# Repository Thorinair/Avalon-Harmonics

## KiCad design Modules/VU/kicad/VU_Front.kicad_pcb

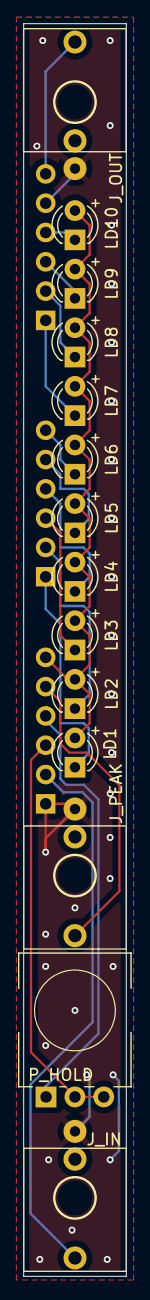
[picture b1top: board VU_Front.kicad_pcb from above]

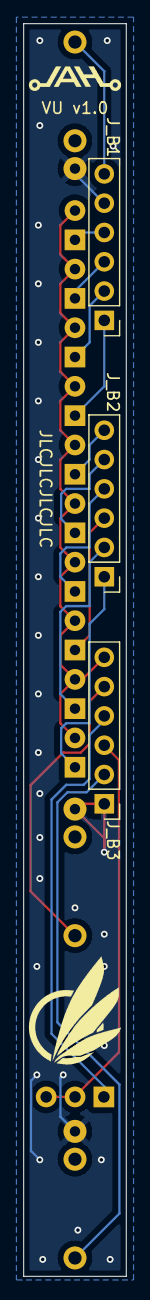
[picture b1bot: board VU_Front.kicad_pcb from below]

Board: 2 copper layers, 8.9 x 108.6 mm, 17 parts (3 on the bottom side), 17 nets.

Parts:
J_B1, J_B2, J_B3: Conn_01x06_Female; PinHeader_1x06_P2.54mm_Vertical
J_IN: PJ301M-12
J_OUT: PJ301M-12
J_PEAK: PJ301M-12
LD1, LD2, LD3, LD4, LD5: LED (YELLOW); LED_D3.0mm_FlatTop
LD6, LD7, LD8: LED (ORANGE); LED_D3.0mm_FlatTop
LD9, LD10: LED (RED); LED_D3.0mm_FlatTop
P_HOLD: A1M; Potentiometer Alpha RD901F-40-00D NoSides

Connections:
+5V: J_B3.6, LD1.2 (A), LD2.2 (A), LD3.2 (A), LD4.2 (A), LD5.2 (A), LD6.2 (A), LD7.2 (A), LD8.2 (A), LD9.2 (A), LD10.2 (A)
GND: J_B1.5, J_B3.1, J_IN.GND, J_OUT.GND, J_PEAK.GND
unnamed: J_B1.1, LD7.1 (K)
unnamed: J_B1.2, LD8.1 (K)
unnamed: J_B1.3, LD9.1 (K)
unnamed: J_B1.4, LD10.1 (K)
unnamed: J_B1.6, J_OUT.SIG
unnamed: J_B2.1, LD1.1 (K)
unnamed: J_B2.2, LD2.1 (K)
unnamed: J_B2.3, LD3.1 (K)
unnamed: J_B2.4, LD4.1 (K)
unnamed: J_B2.5, LD5.1 (K)
unnamed: J_B2.6, LD6.1 (K)
unnamed: J_B3.2, J_IN.SIG
unnamed: J_B3.3, P_HOLD.2, P_HOLD.3
unnamed: J_B3.4, P_HOLD.1
unnamed: J_B3.5, J_PEAK.SIG

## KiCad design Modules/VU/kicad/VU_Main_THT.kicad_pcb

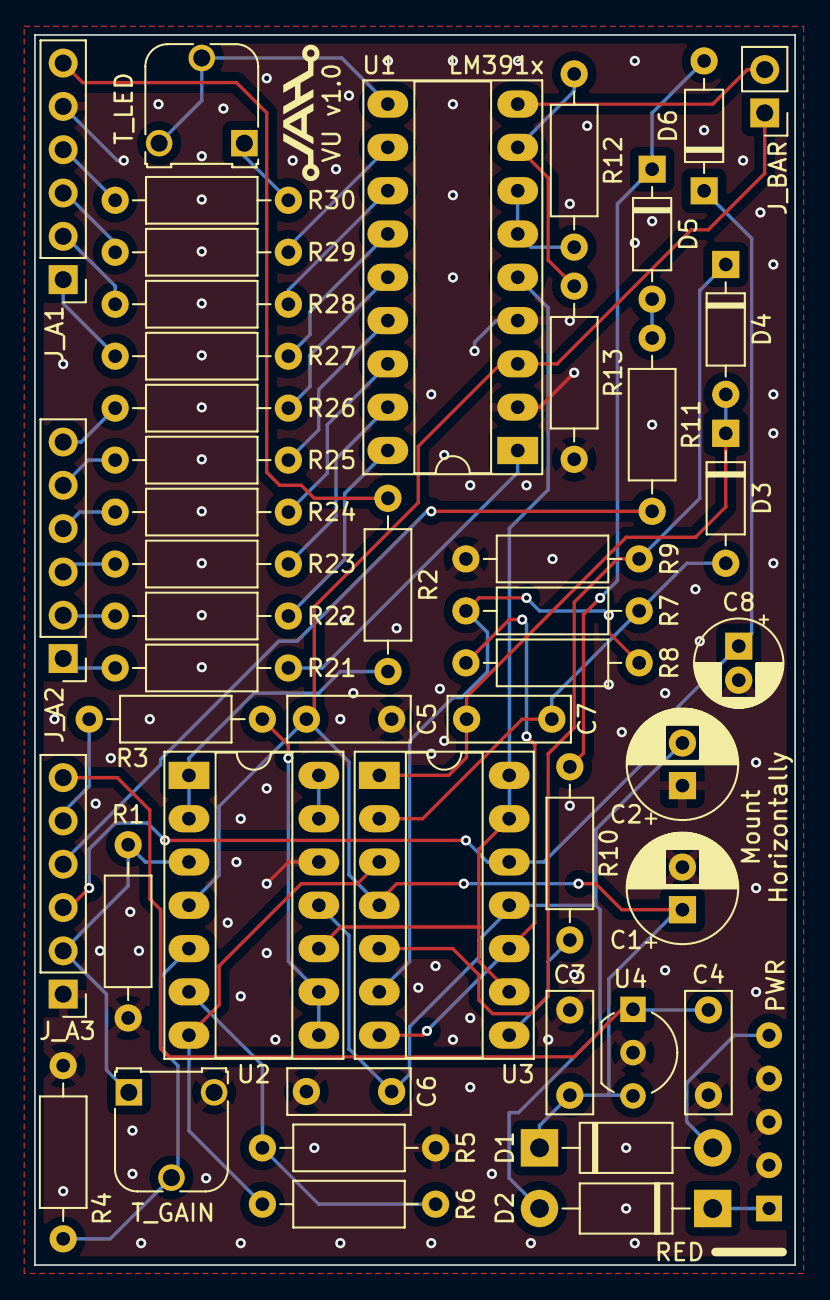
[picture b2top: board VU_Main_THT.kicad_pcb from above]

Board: 2 copper layers, 44.6 x 72.2 mm, 48 parts (0 on the bottom side), 50 nets.

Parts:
C1, C2: 47uF; CP_Radial_D6.3mm_P2.50mm
C3, C4, C5, C6: 0.1uF; C_Disc_D7.0mm_W2.5mm_P5.00mm
C7: 47pF; C_Disc_D7.0mm_W2.5mm_P5.00mm
C8: 10uF; CP_Radial_D5.0mm_P2.00mm
D1, D2: 1N4001; D_DO-41_SOD81_P10.16mm_Horizontal
D3, D4, D5, D6: 1N4148; D_DO-35_SOD27_P7.62mm_Horizontal
J_A1, J_A2, J_A3: Conn_01x06_Male; PinHeader_1x06_P2.54mm_Vertical
J_BAR: Conn_01x02_Male; PinHeader_1x02_P2.54mm_Vertical
PWR1: PWR_5_Pin_Angled; Eurorack Power 5 Pin Angled
R1, R4: 100k; R_Axial_DIN0207_L6.3mm_D2.5mm_P10.16mm_Horizontal
R2, R3, R30: 1k; R_Axial_DIN0207_L6.3mm_D2.5mm_P10.16mm_Horizontal
R5, R13: 22k; R_Axial_DIN0207_L6.3mm_D2.5mm_P10.16mm_Horizontal
R6: 330k; R_Axial_DIN0207_L6.3mm_D2.5mm_P10.16mm_Horizontal
R7, R8, R9, R11, R12, R21, R22, R23, R24, R25, R26, R27, R28, R29: 10k; R_Axial_DIN0207_L6.3mm_D2.5mm_P10.16mm_Horizontal
R10: 100; R_Axial_DIN0207_L6.3mm_D2.5mm_P10.16mm_Horizontal
T_GAIN: B100k; Potentiometer_Runtron_RM-065_Vertical
T_LED: B20k; Potentiometer_Runtron_RM-065_Vertical
U1: LM3914N; DIP-18_W7.62mm_Socket_LongPads
U2, U3: TL074; DIP-14_W7.62mm_Socket_LongPads
U4: 78L05; TO-92_Inline_Wide

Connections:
+5V: C4.1, J_A3.6, U4.1 (VO)
+12V: C1.1, C3.1, C5.1, D1.1 (K), J_BAR.1, U1.3 (V+), U2.4 (V+), U3.4 (V+), U4.3 (VI)
-12V: C2.2, C6.2, D2.2 (A), U2.11 (V-), U3.11 (V-)
/GAIN: R6.1, U2.7, U3.3 (+)
/HOLD_R: C8.1, D6.1 (K), J_A3.3, U3.12 (+)
/HOLD_S: J_A3.4, R11.2
/IN: J_A3.2, R1.2, T_GAIN.1, U2.3 (+)
/OUT_PEAK: J_A3.5, R3.1
/OUT_RAW: J_A1.6, R2.1
/PEAK: U1.5 (SIG), U2.10 (+), U3.9 (-), U3.13 (-), U3.14
/RECT: R8.1, U3.7, U3.10 (+)
GND: C1.2, C2.1, C3.2, C4.2, C5.2, C6.1, C8.2, J_A1.5, J_A3.1, PWR1.2 (GND), R1.1, R4.1, R5.2, R9.1, R13.1, T_GAIN.3, U1.2 (V-), U1.4 (RLO), U2.12 (+), U4.2 (GND)
unnamed: D1.2 (A), PWR1.1 (+12V)
unnamed: D2.1 (K), PWR1.3 (-12V)
unnamed: C7.1, D3.2 (A), R7.2, U3.2 (-)
unnamed: C7.2, D3.1 (K), D4.2 (A), U3.1
unnamed: D4.1 (K), R9.2, U3.5 (+)
unnamed: D5.2 (A), R11.1
unnamed: D5.1 (K), D6.2 (A), R10.1
unnamed: J_A1.1, R27.2
unnamed: J_A1.2, R28.2
unnamed: J_A1.3, R29.2
unnamed: J_A1.4, R30.2
unnamed: J_A2.1, R21.2
unnamed: J_A2.2, R22.2
unnamed: J_A2.3, R23.2
unnamed: J_A2.4, R24.2
unnamed: J_A2.5, R25.2
unnamed: J_A2.6, R26.2
unnamed: J_BAR.2, U1.9 (MODE)
unnamed: R10.2, U3.8
unnamed: R30.1, T_LED.1
unnamed: R21.1, U1.1 (LED1)
unnamed: R22.1, U1.18 (LED2)
unnamed: R23.1, U1.17 (LED3)
unnamed: R24.1, U1.16 (LED4)
unnamed: R25.1, U1.15 (LED5)
unnamed: R26.1, U1.14 (LED6)
unnamed: R27.1, U1.13 (LED7)
unnamed: R28.1, U1.12 (LED8)
unnamed: R29.1, U1.11 (LED9)
unnamed: T_LED.2, T_LED.3, U1.10 (LED10)
unnamed: R12.1, R13.2, U1.8 (REFADJ)
unnamed: R12.2, U1.6 (RHI), U1.7 (REFOUT)
unnamed: R2.2, U2.1, U2.2 (-)
unnamed: R4.2, T_GAIN.2, U2.5 (+)
unnamed: R5.1, R6.2, U2.6 (-)
unnamed: R3.2, U2.8, U2.9 (-)
unnamed: U2.13 (-), U2.14
unnamed: R7.1, R8.2, U3.6 (-)

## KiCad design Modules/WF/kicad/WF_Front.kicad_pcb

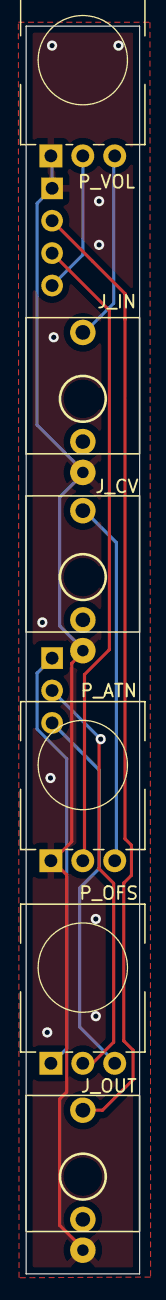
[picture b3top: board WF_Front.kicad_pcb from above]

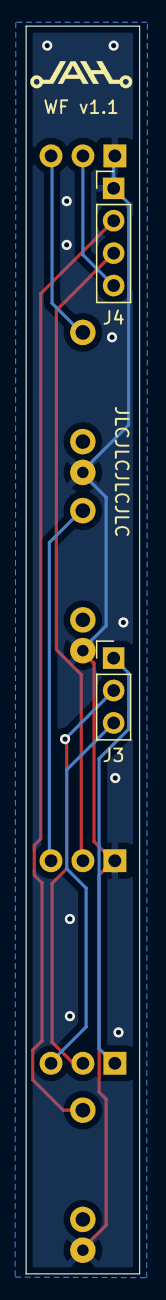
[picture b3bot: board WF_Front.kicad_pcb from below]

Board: 2 copper layers, 8.9 x 97.8 mm, 8 parts (2 on the bottom side), 9 nets.

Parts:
J3: Conn_01x03_Female; PinHeader_1x03_P2.54mm_Vertical
J4: Conn_01x04_Female; PinHeader_1x04_P2.54mm_Vertical
J_CV1: PJ301M-12
J_IN1: PJ301M-12
J_OUT1: PJ301M-12
P_ATN1: B100k; Potentiometer Alpha RD901F-40-00D NoSides
P_OFS1: B100k; Potentiometer Alpha RD901F-40-00D NoSides
P_VOL1: B100k; Potentiometer Alpha RD901F-40-00D NoSides

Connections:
GND: J4.1, J_CV1.GND, J_IN1.GND, J_OUT1.GND, P_ATN1.1, P_VOL1.1
unnamed: J3.1, P_OFS1.1
unnamed: J3.2, P_OFS1.2
unnamed: J3.3, P_OFS1.3
unnamed: J4.2, J_OUT1.SIG
unnamed: J4.3, P_ATN1.2
unnamed: J4.4, P_VOL1.2
unnamed: J_CV1.SIG, P_ATN1.3
unnamed: J_IN1.SIG, P_VOL1.3

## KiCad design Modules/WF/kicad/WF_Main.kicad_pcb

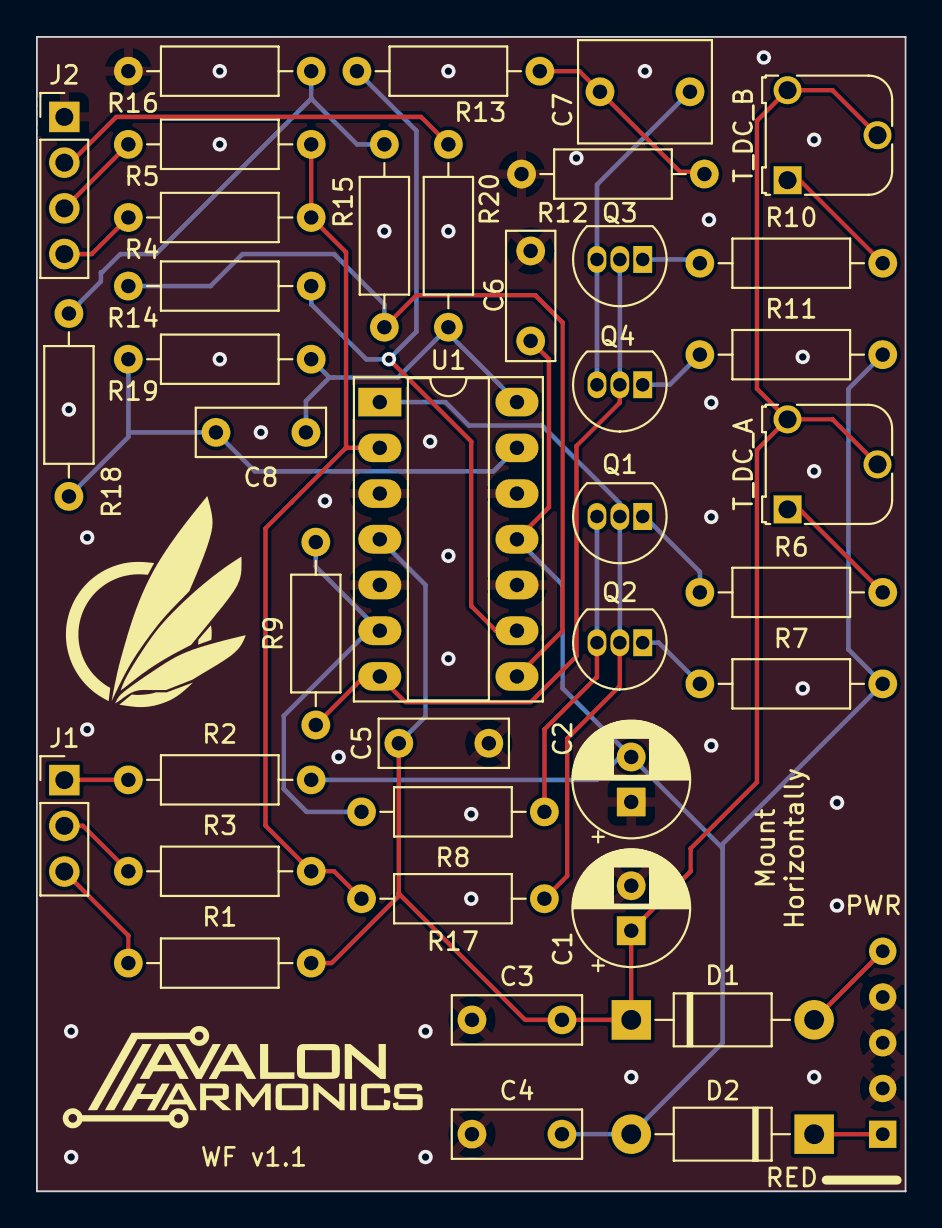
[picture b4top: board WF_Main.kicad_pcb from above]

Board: 2 copper layers, 48.3 x 64.1 mm, 40 parts (0 on the bottom side), 29 nets.

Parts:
C1, C2: 47uF; CP_Radial_D6.3mm_P2.50mm
C3, C4, C5, C6: 0.1uF; C_Disc_D7.0mm_W2.5mm_P5.00mm
C7: 2.2uF (Film); C_Rect_L7.2mm_W5.5mm_P5.00mm_FKS2_FKP2_MKS2_MKP2
C8: 100pF; C_Disc_D7.0mm_W2.5mm_P5.00mm
D1, D2: 1N4001; D_DO-41_SOD81_P10.16mm_Horizontal
J1: Conn_01x03_Male; PinHeader_1x03_P2.54mm_Vertical
J2: Conn_01x04_Male; PinHeader_1x04_P2.54mm_Vertical
PWR1: PWR_5_Pin_Angled; Eurorack Power 5 Pin Angled
Q1, Q3: 2N3906; TO-92_Inline
Q2, Q4: 2N3904; TO-92_Inline
R1, R2: 200k; R_Axial_DIN0207_L6.3mm_D2.5mm_P10.16mm_Horizontal
R3, R4, R5, R12, R15, R17, R18, R19: 100k; R_Axial_DIN0207_L6.3mm_D2.5mm_P10.16mm_Horizontal
R6, R10: 15k; R_Axial_DIN0207_L6.3mm_D2.5mm_P10.16mm_Horizontal
R7, R11: 22k; R_Axial_DIN0207_L6.3mm_D2.5mm_P10.16mm_Horizontal
R8: 10k; R_Axial_DIN0207_L6.3mm_D2.5mm_P10.16mm_Horizontal
R9: 47k; R_Axial_DIN0207_L6.3mm_D2.5mm_P10.16mm_Horizontal
R13: 12k; R_Axial_DIN0207_L6.3mm_D2.5mm_P10.16mm_Horizontal
R14, R16: 180k; R_Axial_DIN0207_L6.3mm_D2.5mm_P10.16mm_Horizontal
R20: 1k; R_Axial_DIN0207_L6.3mm_D2.5mm_P10.16mm_Horizontal
T_DC_A1: B10k; Potentiometer_Runtron_RM-065_Vertical
T_DC_B1: B10k; Potentiometer_Runtron_RM-065_Vertical
U1: TL074; DIP-14_W7.62mm_Socket_LongPads

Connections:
+12V: C1.1, C3.1, C5.1, D1.1 (K), R1.1, T_DC_A1.2, T_DC_A1.3, T_DC_B1.2, T_DC_B1.3, U1.4 (V+)
-12V: C2.2, C4.2, C6.2, D2.2 (A), R2.2, R7.2, R11.2, U1.11 (V-)
/OUT: J2.2, R20.2
GND: C1.2, C2.1, C3.2, C4.1, C5.2, C6.1, J2.1, PWR1.2 (GND), R12.2, R16.2, U1.3 (+), U1.5 (+), U1.10 (+), U1.12 (+)
unnamed: C7.1, R12.1, R13.1
unnamed: C7.2, Q3.3 (C), Q4.3 (C)
unnamed: C8.1, R19.2, R20.1, U1.14
unnamed: C8.2, R18.2, R19.1, U1.13 (-)
unnamed: D1.2 (A), PWR1.1 (+12V)
unnamed: D2.1 (K), PWR1.3 (-12V)
unnamed: J1.1, R2.1
unnamed: J1.2, R3.2
unnamed: J1.3, R1.2
unnamed: J2.3, R5.2
unnamed: J2.4, R4.2
unnamed: Q1.1 (E), R6.2
unnamed: Q1.2 (B), Q2.2 (B), R17.1, U1.1
unnamed: Q1.3 (C), Q2.3 (C), R8.1
unnamed: Q2.1 (E), R7.1
unnamed: Q3.1 (E), R10.2
unnamed: Q3.2 (B), Q4.2 (B), R9.1, U1.7
unnamed: Q4.1 (E), R11.1
unnamed: R6.1, T_DC_A1.1
unnamed: R8.2, R9.2, U1.6 (-)
unnamed: R10.1, T_DC_B1.1
unnamed: R13.2, R14.1, U1.9 (-)
unnamed: R14.2, R15.2, U1.8
unnamed: R15.1, R16.1, R18.1
unnamed: R3.1, R4.1, R5.1, R17.2, U1.2 (-)

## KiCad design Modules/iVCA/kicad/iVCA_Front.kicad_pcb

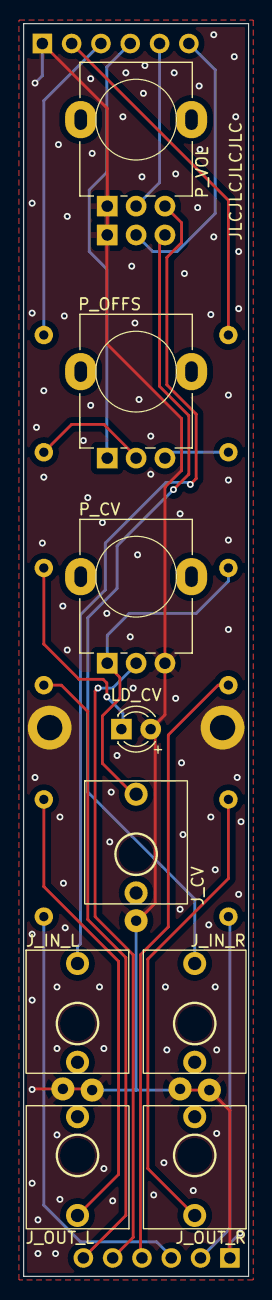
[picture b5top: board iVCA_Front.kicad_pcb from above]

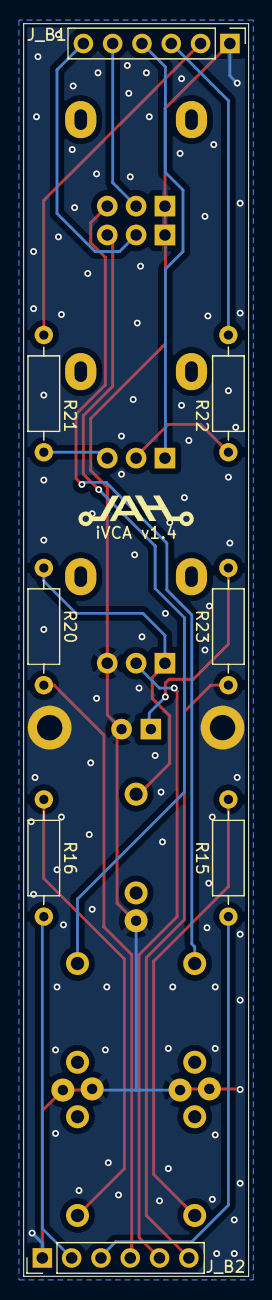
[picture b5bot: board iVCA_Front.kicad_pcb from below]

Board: 2 copper layers, 19.5 x 108.6 mm, 17 parts (8 on the bottom side), 19 nets.

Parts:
J_B1, J_B2: Conn_01x06_Female; PinHeader_1x06_P2.54mm_Vertical
J_CV: PJ301M-12
J_IN_L: PJ301M-12; PJ301M-12 Offset
J_IN_R: PJ301M-12; PJ301M-12 Offset
J_OUT_L: PJ301M-12; PJ301M-12 Offset
J_OUT_R: PJ301M-12; PJ301M-12 Offset
LD_CV: LED (Bi); LED_D3.0mm_FlatTop
P_CV: B50k; Potentiometer Alpha RD901F-40-00D
P_OFFS: B50k; Potentiometer Alpha RD901F-40-00D
P_VOL: A100k; Potentiometer Alpha Dual RD901F-40-00D
R15, R16, R23: 1k; R_Axial_DIN0207_L6.3mm_D2.5mm_P10.16mm_Horizontal
R20, R22: 100k; R_Axial_DIN0207_L6.3mm_D2.5mm_P10.16mm_Horizontal
R21: 10k; R_Axial_DIN0207_L6.3mm_D2.5mm_P10.16mm_Horizontal

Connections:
/INF_L: J_IN_L.SIG, P_VOL.3
/INF_R: J_IN_R.SIG, P_VOL.6
GND: J_B1.1, J_B2.1, J_CV.GND, J_IN_L.GND, J_IN_R.GND, J_OUT_L.GND, J_OUT_R.GND, LD_CV.2 (A), P_CV.3, P_VOL.1, P_VOL.4
unnamed: J_B1.2, R21.1
unnamed: J_B1.3, R22.1
unnamed: J_B1.4, P_OFFS.1
unnamed: J_B1.5, P_VOL.2
unnamed: J_B1.6, P_VOL.5
unnamed: J_B2.2, R16.2
unnamed: J_B2.3, R15.2
unnamed: J_B2.4, R20.1
unnamed: J_B2.5, P_CV.2
unnamed: J_B2.6, R23.2
unnamed: J_CV.SIG, P_CV.1, R20.2
unnamed: J_OUT_L.SIG, R15.1
unnamed: J_OUT_R.SIG, R16.1
unnamed: LD_CV.1 (K), R23.1
unnamed: P_OFFS.2, R22.2
unnamed: P_OFFS.3, R21.2

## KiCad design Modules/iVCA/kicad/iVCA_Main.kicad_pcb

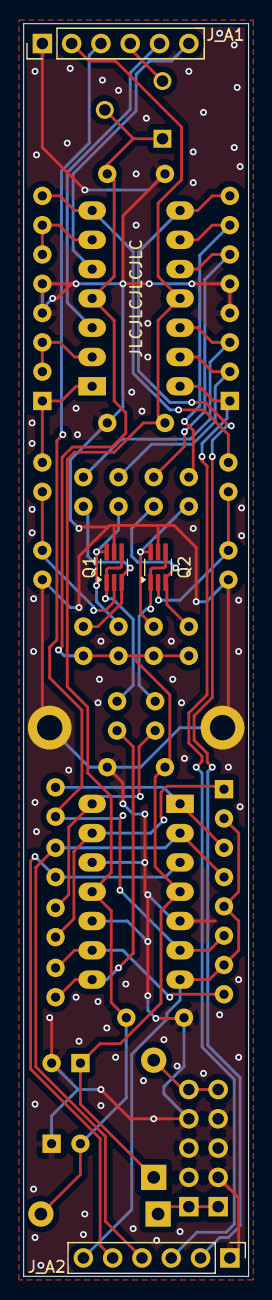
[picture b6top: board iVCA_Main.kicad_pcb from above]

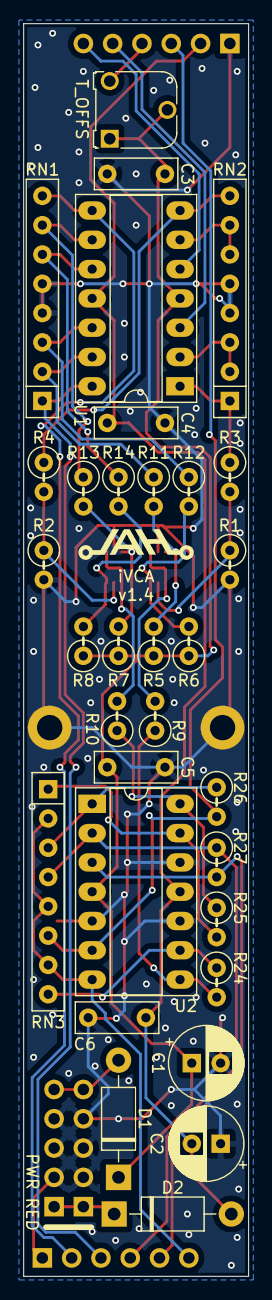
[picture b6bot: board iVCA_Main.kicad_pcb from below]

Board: 2 copper layers, 19.5 x 108.6 mm, 37 parts (33 on the bottom side), 35 nets.

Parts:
C1, C2: 47uF; CP_Radial_D6.3mm_P2.50mm
C3, C4, C5, C6: 0.1uF; C_Disc_D7.0mm_W2.5mm_P5.00mm
D1, D2: 1N4001; D_DO-41_SOD81_P10.16mm_Horizontal
J_A1, J_A2: Conn_01x06_Male; PinHeader_1x06_P2.54mm_Vertical
PWR1: PWR_10_Pin; Eurorack Power 10 Pin
Q1, Q2: BCM847BS; SOT-363_SC-70-6_Handsoldering
R1, R2: 100; R_Axial_DIN0207_L6.3mm_D2.5mm_P2.54mm_Vertical
R3, R4: 100k; R_Axial_DIN0207_L6.3mm_D2.5mm_P2.54mm_Vertical
R5, R6, R7, R8: 20k 0.1%; R_Axial_DIN0207_L6.3mm_D2.5mm_P2.54mm_Vertical
R9, R10, R27: 10k; R_Axial_DIN0207_L6.3mm_D2.5mm_P2.54mm_Vertical
R11, R12, R13, R14: 10k 1%; R_Axial_DIN0207_L6.3mm_D2.5mm_P2.54mm_Vertical
R24, R25: 82k; R_Axial_DIN0207_L6.3mm_D2.5mm_P2.54mm_Vertical
R26: 47k; R_Axial_DIN0207_L6.3mm_D2.5mm_P2.54mm_Vertical
RN1, RN2, RN3: 100k; R_Array_SIP8
T_OFFS: B20k; Potentiometer_Runtron_RM-065_Vertical
U1, U2: TL074; DIP-14_W7.62mm_Socket_LongPads

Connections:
+12V: C1.1, C3.1, C5.1, D1.1 (K), R5.1, R6.1, R7.1, R8.1, T_OFFS.1, T_OFFS.2, U1.4 (V+), U2.4 (V+)
-12V: C2.2, C4.2, C6.2, D2.2 (A), J_A1.2, U1.11 (V-), U2.11 (V-)
/CTRL_L: R9.1, R24.2, U2.8
/CTRL_R: R10.1, R25.1, U2.14
/IN_L: J_A1.5, U1.3 (+)
/IN_R: J_A1.6, U1.5 (+)
/LED: J_A2.6, RN3.2 (R1.2), RN3.5 (R3.1), RN3.7 (R4.1), U2.7
/OFFS: J_A1.3, R26.2, RN3.6 (R3.2), U2.6 (-)
/OUT_L: J_A2.3, RN1.1 (R1.1), U1.14
/OUT_R: J_A2.2, RN1.8 (R4.2), U1.8
GND: C1.2, C2.1, C3.2, C4.1, C5.2, C6.1, J_A1.1, J_A2.1, PWR1.2 (GND), Q1.5 (B2), Q2.5 (B2), R1.2, R2.2, RN1.4 (R2.2), RN1.5 (R3.1), RN2.4 (R2.2), RN2.5 (R3.1), U2.5 (+), U2.10 (+), U2.12 (+)
unnamed: D1.2 (A), PWR1.1 (+12V)
unnamed: D2.1 (K), PWR1.3 (-12V)
unnamed: J_A1.4, T_OFFS.3
unnamed: J_A2.4, R27.1, RN3.4 (R2.2), U2.2 (-)
unnamed: J_A2.5, R27.2, U2.3 (+)
unnamed: Q1.2 (B1), R1.1, R3.2
unnamed: Q1.6 (C1), R5.2, R11.2
unnamed: Q1.1 (E1), Q1.4 (E2), R9.2
unnamed: Q1.3 (C2), R6.2, R12.2
unnamed: Q2.2 (B1), R2.1, R4.2
unnamed: Q2.6 (C1), R7.2, R13.2
unnamed: Q2.1 (E1), Q2.4 (E2), R10.2
unnamed: Q2.3 (C2), R8.2, R14.2
unnamed: R11.1, RN1.2 (R1.2), U1.13 (-)
unnamed: R12.1, RN1.3 (R2.1), U1.12 (+)
unnamed: R14.1, RN1.6 (R3.2), U1.10 (+)
unnamed: R13.1, RN1.7 (R4.1), U1.9 (-)
unnamed: R3.1, RN2.1 (R1.1), U1.1
unnamed: RN2.2 (R1.2), RN2.3 (R2.1), U1.2 (-)
unnamed: RN2.6 (R3.2), RN2.7 (R4.1), U1.6 (-)
unnamed: R4.1, RN2.8 (R4.2), U1.7
unnamed: R25.2, RN3.1 (R1.1), U2.13 (-)
unnamed: R26.1, RN3.3 (R2.1), U2.1
unnamed: R24.1, RN3.8 (R4.2), U2.9 (-)
